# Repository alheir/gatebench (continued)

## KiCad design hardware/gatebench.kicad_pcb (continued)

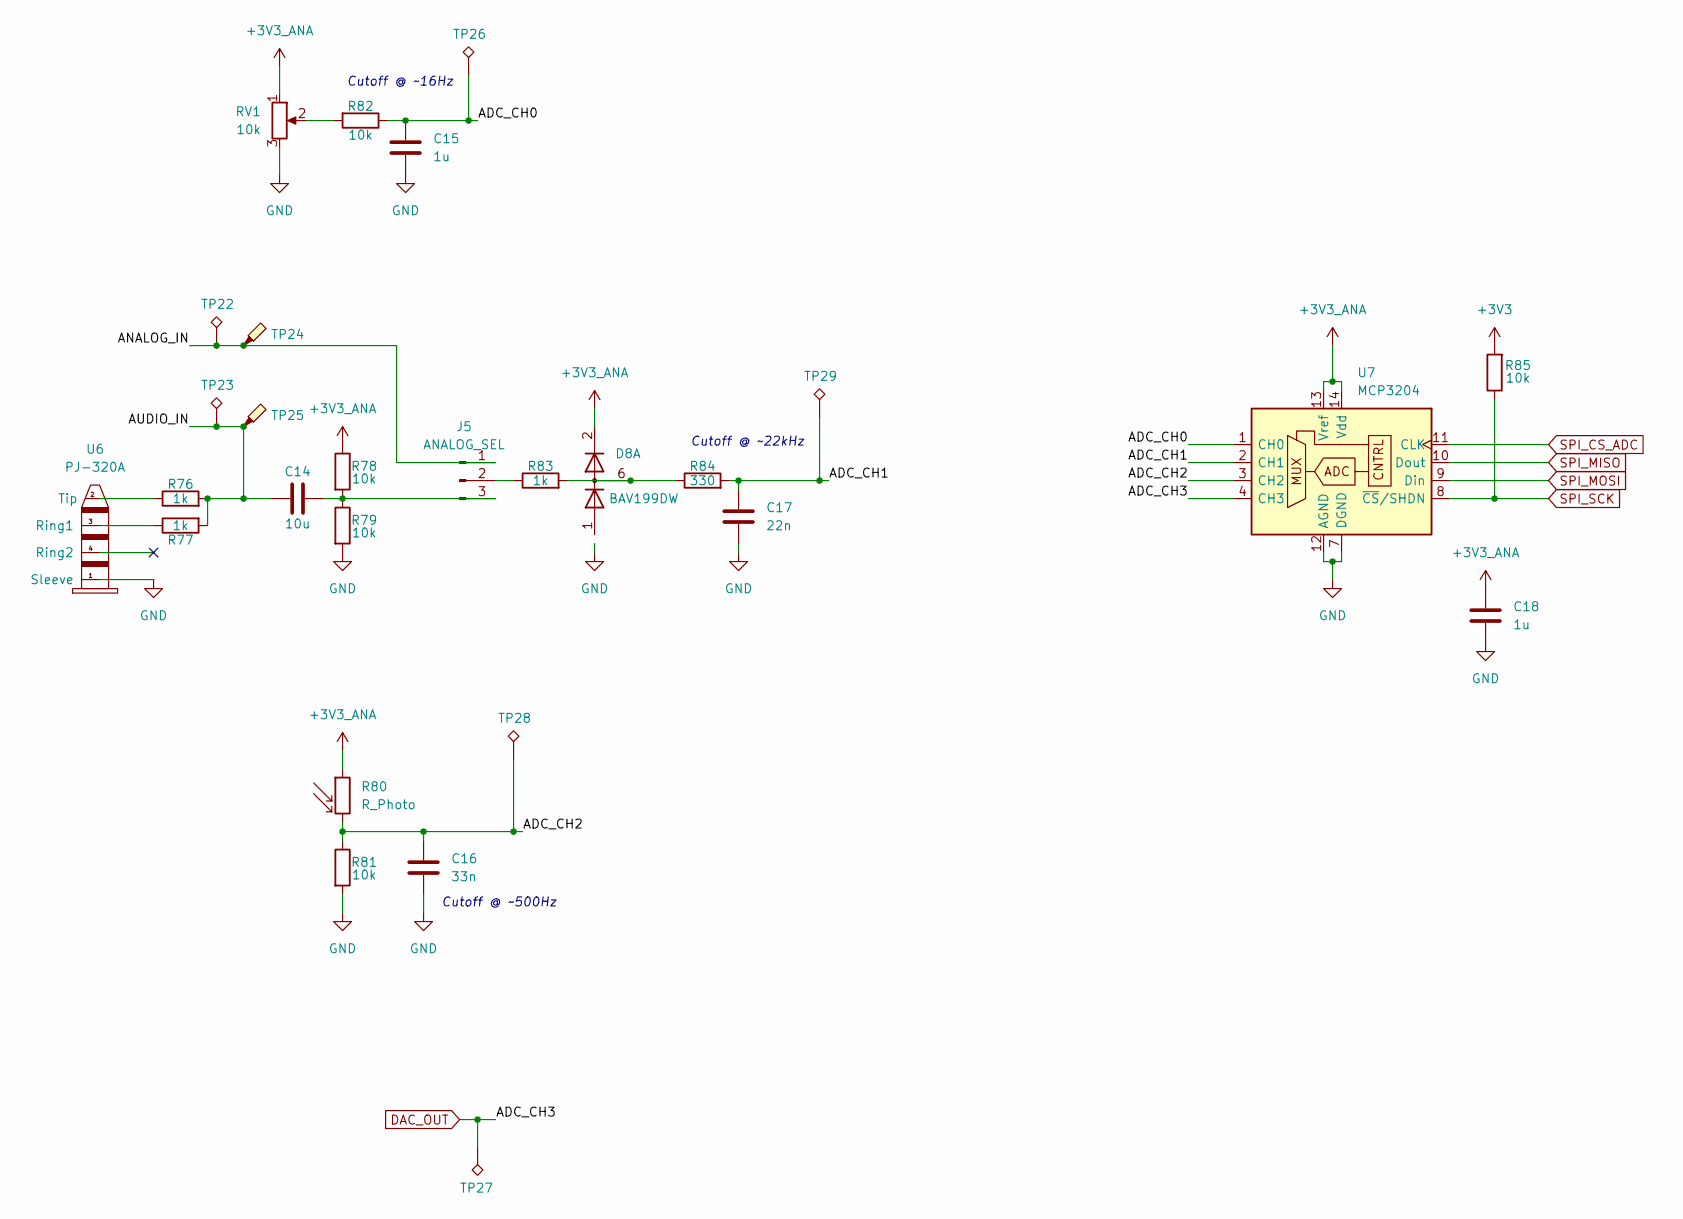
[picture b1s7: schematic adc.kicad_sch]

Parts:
C14: 10u; C_0603_1608Metric_Pad1.08x0.95mm_HandSolder; JLCPCB C1705
C15, C18: 1u; C_0603_1608Metric_Pad1.08x0.95mm_HandSolder; JLCPCB C1705
C16: 33n; C_0603_1608Metric_Pad1.08x0.95mm_HandSolder; JLCPCB C1705
C17: 22n; C_0603_1608Metric_Pad1.08x0.95mm_HandSolder; JLCPCB C1705
D8: BAV199DW; SOT-363_SC-70-6
J5: ANALOG_SEL; PinHeader_1x03_P2.54mm_Vertical
R76, R77, R83: 1k; R_0603_1608Metric; JLCPCB C22356621
R78, R79, R81, R82, R85: 10k; R_0603_1608Metric; JLCPCB C22356621
R80: R_Photo; R_LDR_7x6mm_P5.1mm_Vertical
R84: 330; R_0603_1608Metric; JLCPCB C22356621
RV1: 10k; Potentiometer_Alps_RK09K_Single_Vertical; LCSC Part # C470307
TP22, TP23, TP26, TP27, TP28, TP29: TestPoint_Alt; PinHeader_1x01_P2.54mm_Vertical
TP24, TP25: TestPoint_Probe; TestPoint_Loop_D2.60mm_Drill0.9mm_Beaded
U6: PJ-320A; LCSC Part # C18185602
U7: MCP3204; SOIC-14_3.9x8.7mm_P1.27mm

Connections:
+3V3: R85.2; also elsewhere on the board
+3V3_ANA: C18.1, D8.2 (K2), R78.1, R80.1, RV1.1, U7.13 (Vref), U7.14 (Vdd); also elsewhere on the board
/ADC/ADC_CH0: C15.1, R82.1, TP26.1 (1_1), U7.1 (CH0)
/ADC/ADC_CH1: C17.1, R84.2, TP29.1 (1_1), U7.2 (CH1)
/ADC/ADC_CH2: C16.1, R80.2, R81.1, TP28.1 (1_1), U7.3 (CH2)
/ADC/ANALOG_IN: J5.1, TP22.1 (1_1), TP24.1 (1_1)
/ADC/AUDIO_IN: C14.2, R76.2, R77.2, TP23.1 (1_1), TP25.1 (1_1)
DAC_OUT: TP27.1 (1_1), U7.4 (CH3); also elsewhere on the board
GND: C15.2, C16.2, C17.2, C18.2, R79.2, R81.2, RV1.3, U6.1 (Sleeve), U7.7 (DGND), U7.12 (AGND); also elsewhere on the board
unnamed: D8.6 (K3A4), R83.2, R84.1
unnamed: J5.2, R83.1
unnamed: C14.1, J5.3, R78.2, R79.1
unnamed: R82.2, RV1.2
unnamed: R77.1, U6.3 (Ring1)
unnamed: R76.1, U6.2 (Tip)
PMOD_7: U7.10 (Dout); also elsewhere on the board
PMOD_8: U7.9 (Din); also elsewhere on the board
PMOD_9: R85.1, U7.8 (~CS/SHDN); also elsewhere on the board
SPI_CS_ADC: U7.11 (CLK); also elsewhere on the board

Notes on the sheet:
Cutoff @ ~22kHz
Cutoff @ ~500Hz
Cutoff @ ~16Hz

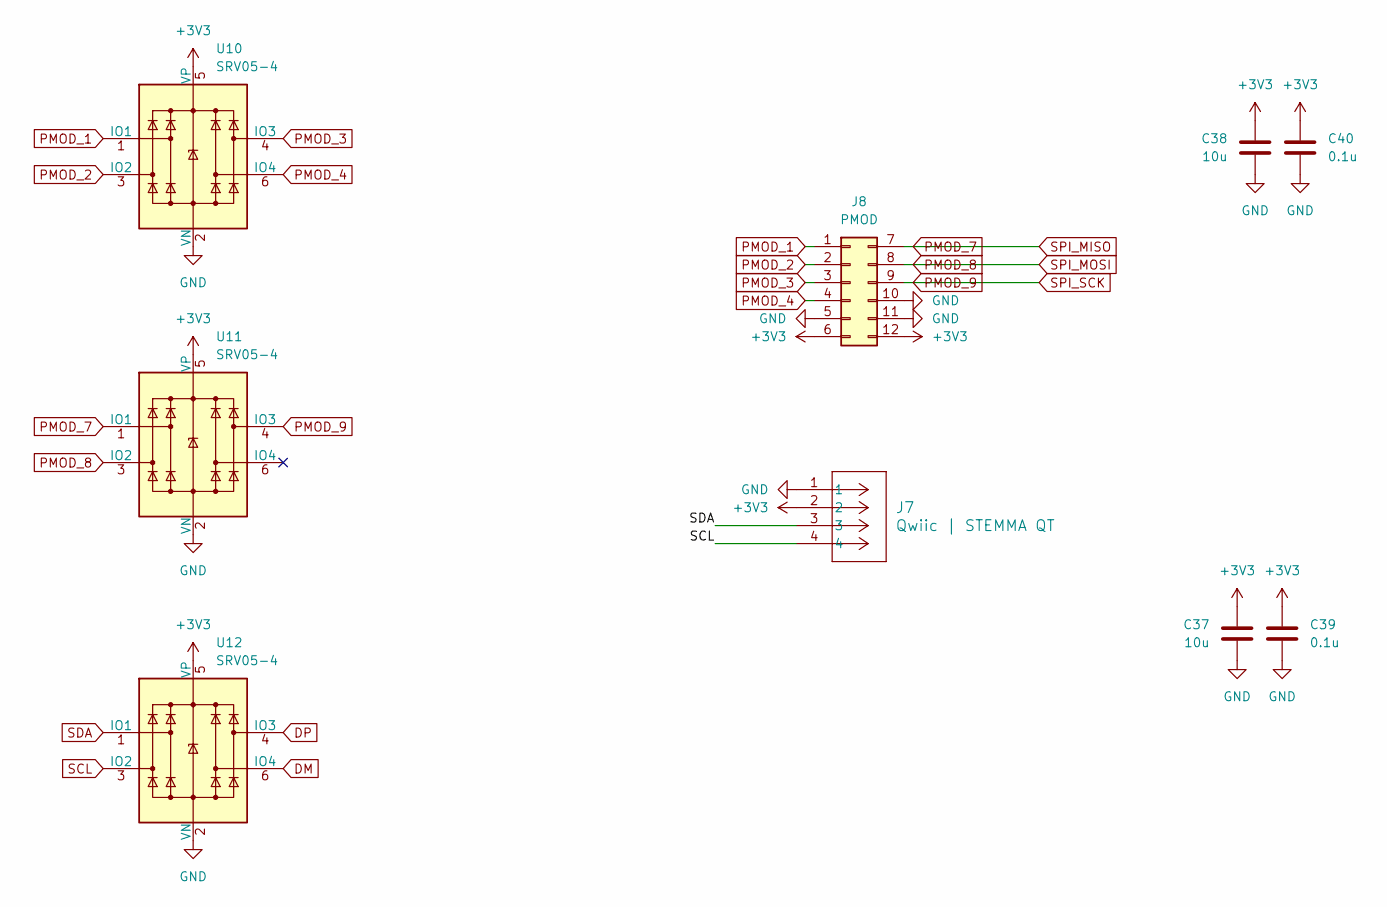
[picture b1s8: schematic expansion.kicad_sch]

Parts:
C37, C38: 10u; C_0603_1608Metric_Pad1.08x0.95mm_HandSolder; JLCPCB C1705
C39, C40: 0.1u; C_0603_1608Metric_Pad1.08x0.95mm_HandSolder; JLCPCB C1705
J7: Qwiic | STEMMA QT; CONN_SM04B_JST; LCSC Part # C51940130
J8: PMOD; PinHeader_2x06_P2.54mm_Horizontal
U10, U11, U12: SRV05-4; SOT-23-5; LCSC Part # C558418

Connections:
+3V3: C37.1, C38.1, C39.1, C40.1, J7.2, J8.6, J8.12, U10.5 (VP), U11.5 (VP), U12.5 (VP); also elsewhere on the board
DP: U12.4 (IO3); also elsewhere on the board
GND: C37.2, C38.2, C39.2, C40.2, J7.1, J8.5, J8.10, J8.11, U10.2 (VN), U11.2 (VN), U12.2 (VN); also elsewhere on the board
PMOD_1: J8.1, U10.1 (IO1)
PMOD_2: J8.2, U10.3 (IO2)
PMOD_3: J8.3, U10.4 (IO3)
PMOD_4: J8.4, U10.6 (IO4)
PMOD_7: J8.7, U11.1 (IO1); also elsewhere on the board
PMOD_8: J8.8, U11.3 (IO2); also elsewhere on the board
PMOD_9: J8.9, U11.4 (IO3); also elsewhere on the board
SCL: J7.4, U12.3 (IO2); also elsewhere on the board
SDA: J7.3, U12.1 (IO1); also elsewhere on the board

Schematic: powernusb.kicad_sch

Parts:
C4: 1nF/250V; C_0603_1608Metric_Pad1.08x0.95mm_HandSolder; JLCPCB C277510
C5, C7, C10: 10u; C_0603_1608Metric_Pad1.08x0.95mm_HandSolder; JLCPCB C1705
C6, C8, C9, C11: 0.1u; C_0603_1608Metric_Pad1.08x0.95mm_HandSolder; JLCPCB C1705
D2: PMEG2010EH; SOT-583-8
D3: PMEG2010EH; Nexperia_CFP3_SOD-123W
D4: SMF5V0A; D_SMF
D5: BAT54J; SOT-323_SC-70
D6, D7: RED; LED_0603_1608Metric; LCSC Part # C2286
FB1: BLM21PG600SN1D; L_0805_2012Metric; LCSC Part # C18305
FB2: BLM18HE152SN1D; L_0603_1608Metric; LCSC Part # C82155
J1: Conn_01x02_Pin; Molex_KK-254_AE-6410-02A_1x02_P2.54mm_Vertical
J2: Screw_Terminal_01x02; TerminalBlock_Phoenix_MKDS-1,5-2-5.08_1x02_P5.08mm_Horizont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
J3: USB_B; USB_B_OST_USB-B1HSxx_Horizontal; JLCPCB C456014
JP3: Jumper_2_Open; TestPoint_2Pads_Pitch2.54mm_Drill0.8mm
R21: 1M; R_0603_1608Metric; JLCPCB C22356623
R22: 4k7; R_0603_1608Metric; JLCPCB C22356621; not fitted
R23: 4k7; R_0603_1608Metric; JLCPCB C22356621
R24: 1k; R_0603_1608Metric; JLCPCB C22356621
R25: 470; R_0603_1608Metric; JLCPCB C22356621
TH1: Ihold=750mA; R_1206_3216Metric
TP8, TP9, TP18, TP20: TestPoint_Probe; TestPoint_Loop_D2.60mm_Drill0.9mm_Beaded
TP10, TP11, TP12, TP13, TP14, TP15, TP16, TP17, TP19, TP21: TestPoint_Alt; PinHeader_1x01_P2.54mm_Vertical
U3: AP2112K-3.3; SOT-23-5; JLCPCB C51118
U4: CH340N; JEITA_SOIC-8_3.9x4.9mm_P1.27mm

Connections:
+3V3: C7.1, C8.1, C9.1, FB2.1, R22.2, R25.2, TP13.1 (1_1), U3.5 (VOUT), U4.5 (VCC), U4.8 (V3); also elsewhere on the board
+3V3_ANA: C10.1, C11.1, FB2.2, TP17.1 (1_1); also elsewhere on the board
+3V3_UP: R23.2; also elsewhere on the board
+5V: C5.1, C6.1, D2.2 (A), FB1.2, R24.2, TP14.1 (1_1), U3.1 (VIN), U3.3 (EN); also elsewhere on the board
+5V_UP: JP3.2 (B); also elsewhere on the board
/Power & USB/preVBUS: D3.2 (A), J1.2, J2.1, TP9.1 (1_1)
DM: J3.2 (D-), TP11.1 (1_1), U4.2 (UD-)
DP: J3.3 (D+), TP12.1 (1_1), U4.1 (UD+); also elsewhere on the board
GND: C4.1, C5.2, C6.2, C7.2, C8.2, C9.2, C10.2, C11.2, D4.2 (A2), D6.1 (K), D7.1 (K), J1.1, J2.2, J3.4 (GND), R21.2, TP8.1 (1_1), TP18.1 (1_1), TP19.1 (1_1), TP20.1 (1_1), TP21.1 (1_1), U3.2 (GND), U4.3 (GND); also elsewhere on the board
unnamed: D2.1 (K), JP3.1 (A)
unnamed: D4.1 (A1), FB1.1, TH1.1
unnamed: D5.1 (K), U4.6 (TXD)
unnamed: D6.2 (A), R24.1
unnamed: D7.2 (A), R25.1
unnamed: C4.2, J3.SH (Shield), R21.1
UART_RX: D5.2 (A), R23.1, TP15.1 (1_1); also elsewhere on the board
UART_TX: R22.1, TP16.1 (1_1), U4.7 (RXD); also elsewhere on the board
VBUS: D3.1 (K), J3.1 (VBUS), TH1.2, TP10.1 (1_1)

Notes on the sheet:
Connected to driver's RXD
Enables powering UPduino from GateBench
Connected to driver's TXD

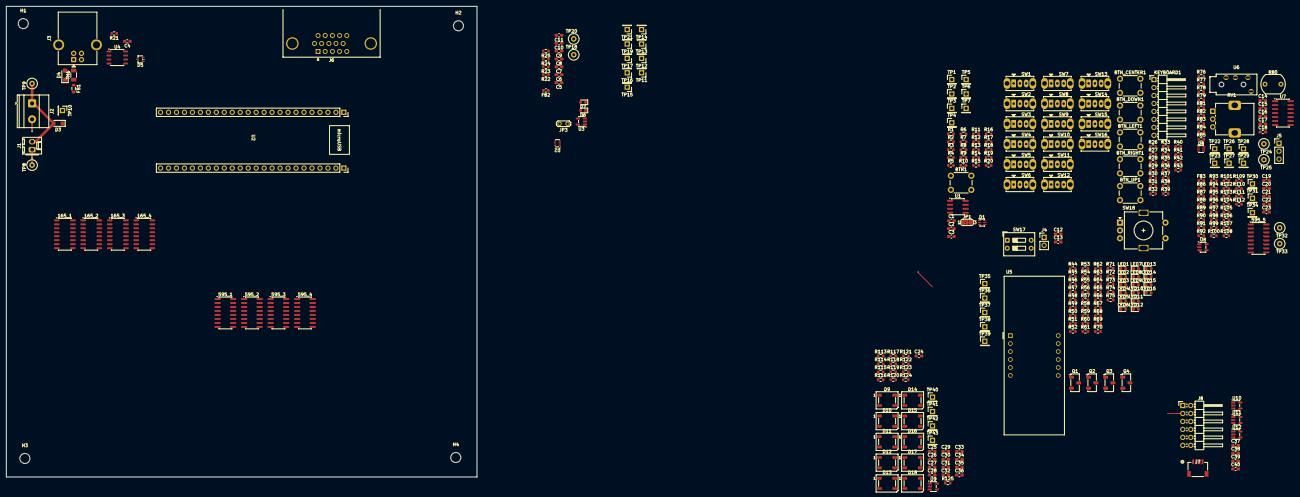
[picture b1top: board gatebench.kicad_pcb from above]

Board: 4 copper layers, 150.0 x 150.0 mm, 311 parts (0 on the bottom side), 227 nets.
